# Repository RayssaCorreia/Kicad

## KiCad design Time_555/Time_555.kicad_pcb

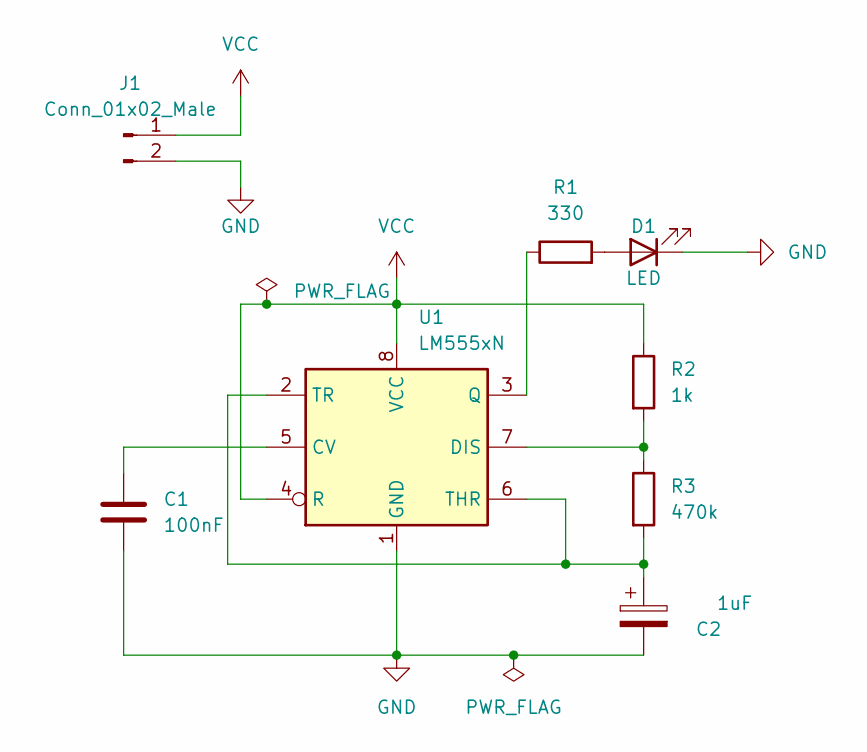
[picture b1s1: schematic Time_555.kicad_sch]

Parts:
C1: 100nF; C_Disc_D3.0mm_W1.6mm_P2.50mm
C2: 1uF; CP_Radial_D5.0mm_P2.50mm
D1: LED; LED_D3.0mm
J1: Conn_01x02_Male; PinHeader_1x02_P2.54mm_Vertical
R1: 330; R_Axial_DIN0204_L3.6mm_D1.6mm_P7.62mm_Horizontal
R2: 1k; R_Axial_DIN0204_L3.6mm_D1.6mm_P7.62mm_Horizontal
R3: 470k; R_Axial_DIN0204_L3.6mm_D1.6mm_P7.62mm_Horizontal
U1: LM555xN; DIP-8_W7.62mm

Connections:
GND: C1.2, C2.2, D1.1 (K), J1.2, U1.1 (GND)
unnamed: C1.1, U1.5 (CV)
unnamed: C2.1, R3.2, U1.2 (TR), U1.6 (THR)
unnamed: D1.2 (A), R1.2
unnamed: R1.1, U1.3 (Q)
unnamed: R2.2, R3.1, U1.7 (DIS)
VCC: J1.1, R2.1, U1.4 (R), U1.8 (VCC)

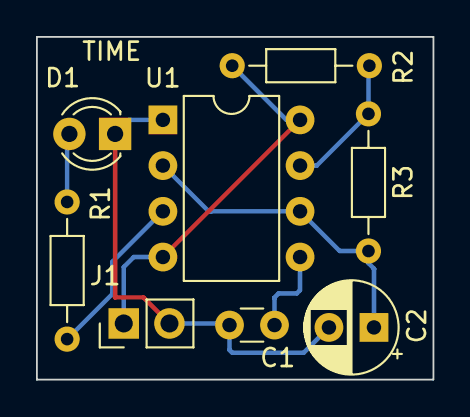
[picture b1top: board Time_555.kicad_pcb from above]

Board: 2 copper layers, 22.0 x 19.0 mm, 8 parts (0 on the bottom side), 7 nets.
